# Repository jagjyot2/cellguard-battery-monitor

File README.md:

# CellGuard — Intelligent 21700 Li-Ion Battery Pack Monitor & Health Analytics

[-amber.svg)](./hardware/SAFETY-AND-TEST-PROCEDURE.md)

**CellGuard** (`cellguard-battery-monitor`) is an end-to-end embedded + hardware + analytics platform for monitoring **1S–6S 21700 Li-Ion battery packs** (optimized for **4S 14.8 V** and **6S 22.2 V** packs). It combines a KiCad 8 Kelvin-shunt instrumentation PCB, modular ESP32 PlatformIO C++ firmware, a BenchTwin digital-twin staging package, a FastAPI + SQLite analytics backend, and a dark-mode React + TypeScript telemetry dashboard.

> **CRITICAL SAFETY NOTICE**  
> **CellGuard is strictly a NON-INVASIVE, READ-ONLY telemetry and health analytics instrument.**  
> It **MUST ONLY** be used **alongside an external commercial BMS and an inline main fuse**.  
> CellGuard implements **NO cell balancing**, **NO battery charging**, and **NO high-current MOSFET switching**.  
> Review [`hardware/SAFETY-AND-TEST-PROCEDURE.md`](./hardware/SAFETY-AND-TEST-PROCEDURE.md) before applying power.

---

## Key Capabilities

- **Precision Current & Bus Sensing (`INA226`)**: 16-bit I2C shunt/bus monitoring across a **4-wire Kelvin `1.0 mΩ` shunt** with datasheet `CAL` register math, hardware `ALERT` interrupt (`GPIO16`), and 2-point gain/offset calibration.
- **Protected 1S–6S Cell Tap Monitoring**: `100 mA` PPTC polyfuses (`F1..F6`), `SMAJ28A` TVS surge clamping (`D1..D6`), `0.1%` high-impedance dividers, `BAT54S` ADC clamps, and an `8:1` analog MUX (`CD74HC4051` + `2.048 V` `LM4040` precision reference) with bus-sum cross-check.
- **4-Channel Thermal Runaway Array**: Steinhart-Hart NTC thermistor probes (`GPIO39/34/35/32`) with open/short wire fault detection and sliding-window OLS `dT/dt` (`°C/min`) thermal runaway derivative alarms.
- **Battery Health Analytics Engine**:
  - **OCV + Coulomb SoC Fusion**: Trapezoidal mAh/Wh integrator fused during rest with an IR-compensated 19-point 21700 NMC/INR OCV lookup table.
  - **Dynamic DC Internal Resistance (`R_dc = -ΔV / ΔI`)**: Automatic load-step resistance estimator tracking pack and per-cell impedance growth.
  - **State of Health (`SoH %`)**: Combines capacity retention fade and internal resistance growth.
- **Interactive Dashboard & CLI Calibration**: Dark-mode React + TypeScript UI served directly at `/`, 4S/6S bench discharge replay, configurable alarm rules, CSV history export, and `calibration_cli.py` + ESP32 NVS CRC16-protected serial calibration.

---

## Repository Structure

```text
06-CELLGUARD/
├── firmware/                  # PlatformIO ESP32 C++ firmware (INA226, NTC, MUX, Analytics, NVS CLI)
├── simulation/                # Simulator-independent HAL, Wokwi/BenchTwin adapters, scenarios & support matrix
├── wokwi/                     # Active Wokwi diagram.json, wokwi.toml, & custom I2C/MUX chip stubs
├── backend/                   # FastAPI REST API, SQLite DB, dataset replay & built dashboard assets
├── dashboard/                 # React + TypeScript + Vite dark-mode dashboard source
├── hardware/                  # KiCad 8 schematic, PCB, netlist, BOM, Gerbers & Safety Guide
├── benchtwin/                 # Preserved BenchTwin .btw workspace, JSON circuit, netlist, BOM & 3D STL enclosure
├── tests/                     # Pytest verification suite (INA226, SoC/SoH/R_dc, thermal, API/CLI, Wokwi/HAL)
├── docs/ARCHITECTURE.md       # Hardware/firmware math & system design specification
├── calibration_cli.py         # Two-point shunt & voltage divider calibration utility
└── ROADMAP.md                 # Engineering milestones & future roadmap
```

---

## Quick Start

### 1. Run Backend & Web Dashboard
```bash
pip install -r requirements.txt
uvicorn backend.main:app --host 127.0.0.1 --port 8006
```
Open **`http://127.0.0.1:8006/`** in your browser.

*(Optional)* Rebuild the React + TypeScript dashboard frontend into `backend/static/`:
```bash
cd dashboard
npm install
npm run build
```

### 2. Build ESP32 Firmware & Run Wokwi Simulation
```bash
cd firmware
pio run
```
`wokwi/wokwi.toml` points directly to `firmware/.pio/build/esp32dev/firmware.bin` and `firmware.elf`.
- Open `wokwi/` in VS Code with the **Wokwi Simulator** extension, or run headless with `WOKWI_CLI_TOKEN` set (`wokwi-cli wokwi --timeout 10000`).
- See [`wokwi/README.md`](./wokwi/README.md) and [`simulation/documentation/COMPONENT-SUPPORT-MATRIX.md`](./simulation/documentation/COMPONENT-SUPPORT-MATRIX.md) for natively supported Wokwi parts (`board-esp32-devkit-c-v4`, `wokwi-ntc-temperature-sensor`, `wokwi-potentiometer`, `wokwi-led`) vs. custom chips (`chip-ina226`, `chip-cd74hc4051`).
- **BenchTwin Reactivation**: The original `benchtwin/` digital-twin package is preserved intact; see [`simulation/adapters/benchtwin/README.md`](./simulation/adapters/benchtwin/README.md) to reactivate BenchTwin in the future.

### 3. Run Calibration CLI Utility
```bash
python calibration_cli.py --series-cells 4 --capacity-mah 5000 --shunt-mohm 1.0 \
  --curr-meas1 0.02 --curr-ref1 0.00 --curr-meas2 19.85 --curr-ref2 20.00
```

### 4. Run Automated Test Suite
```bash
pytest -v
```

---

## Documentation
- [Hardware Safety & Conservative Bench Test Procedure](./hardware/SAFETY-AND-TEST-PROCEDURE.md)
- [PCB Assembly & Calibration Guide](./hardware/ASSEMBLY-GUIDE.md)
- [System Architecture & Analytics Math](./docs/ARCHITECTURE.md)
- [Wokwi Simulation Setup](./wokwi/README.md)
- [Simulation Component Support Matrix](./simulation/documentation/COMPONENT-SUPPORT-MATRIX.md)
- [BenchTwin Adapter & Reactivation Guide](./simulation/adapters/benchtwin/README.md)
- [BenchTwin Simulation Notes](./benchtwin/BENCHTWIN-SIMULATION-NOTES.md)
- [Development Roadmap](./ROADMAP.md)

## License
Released under the [MIT License](./LICENSE).

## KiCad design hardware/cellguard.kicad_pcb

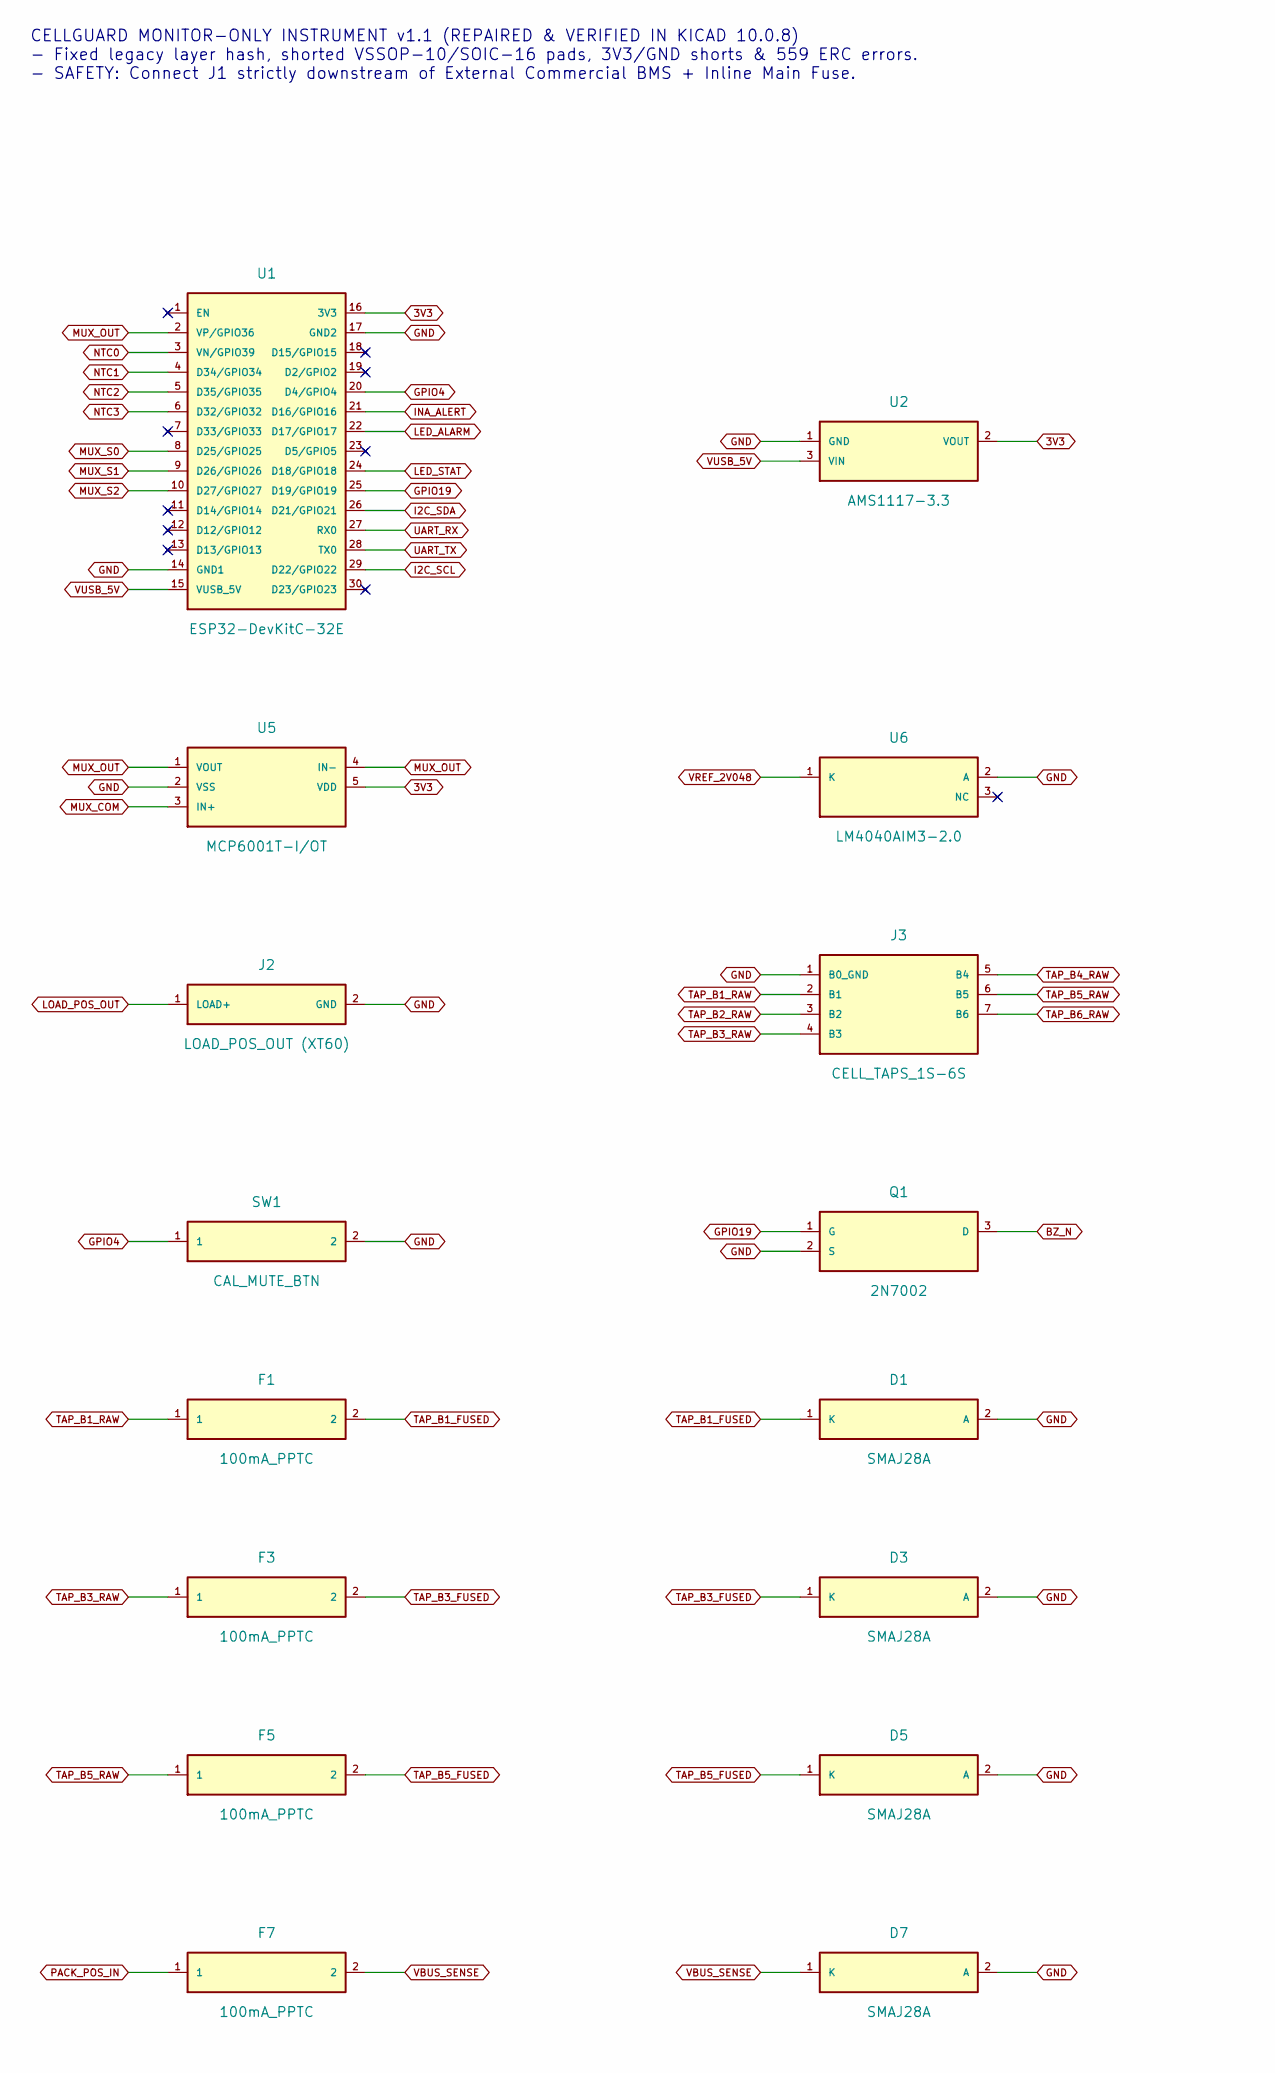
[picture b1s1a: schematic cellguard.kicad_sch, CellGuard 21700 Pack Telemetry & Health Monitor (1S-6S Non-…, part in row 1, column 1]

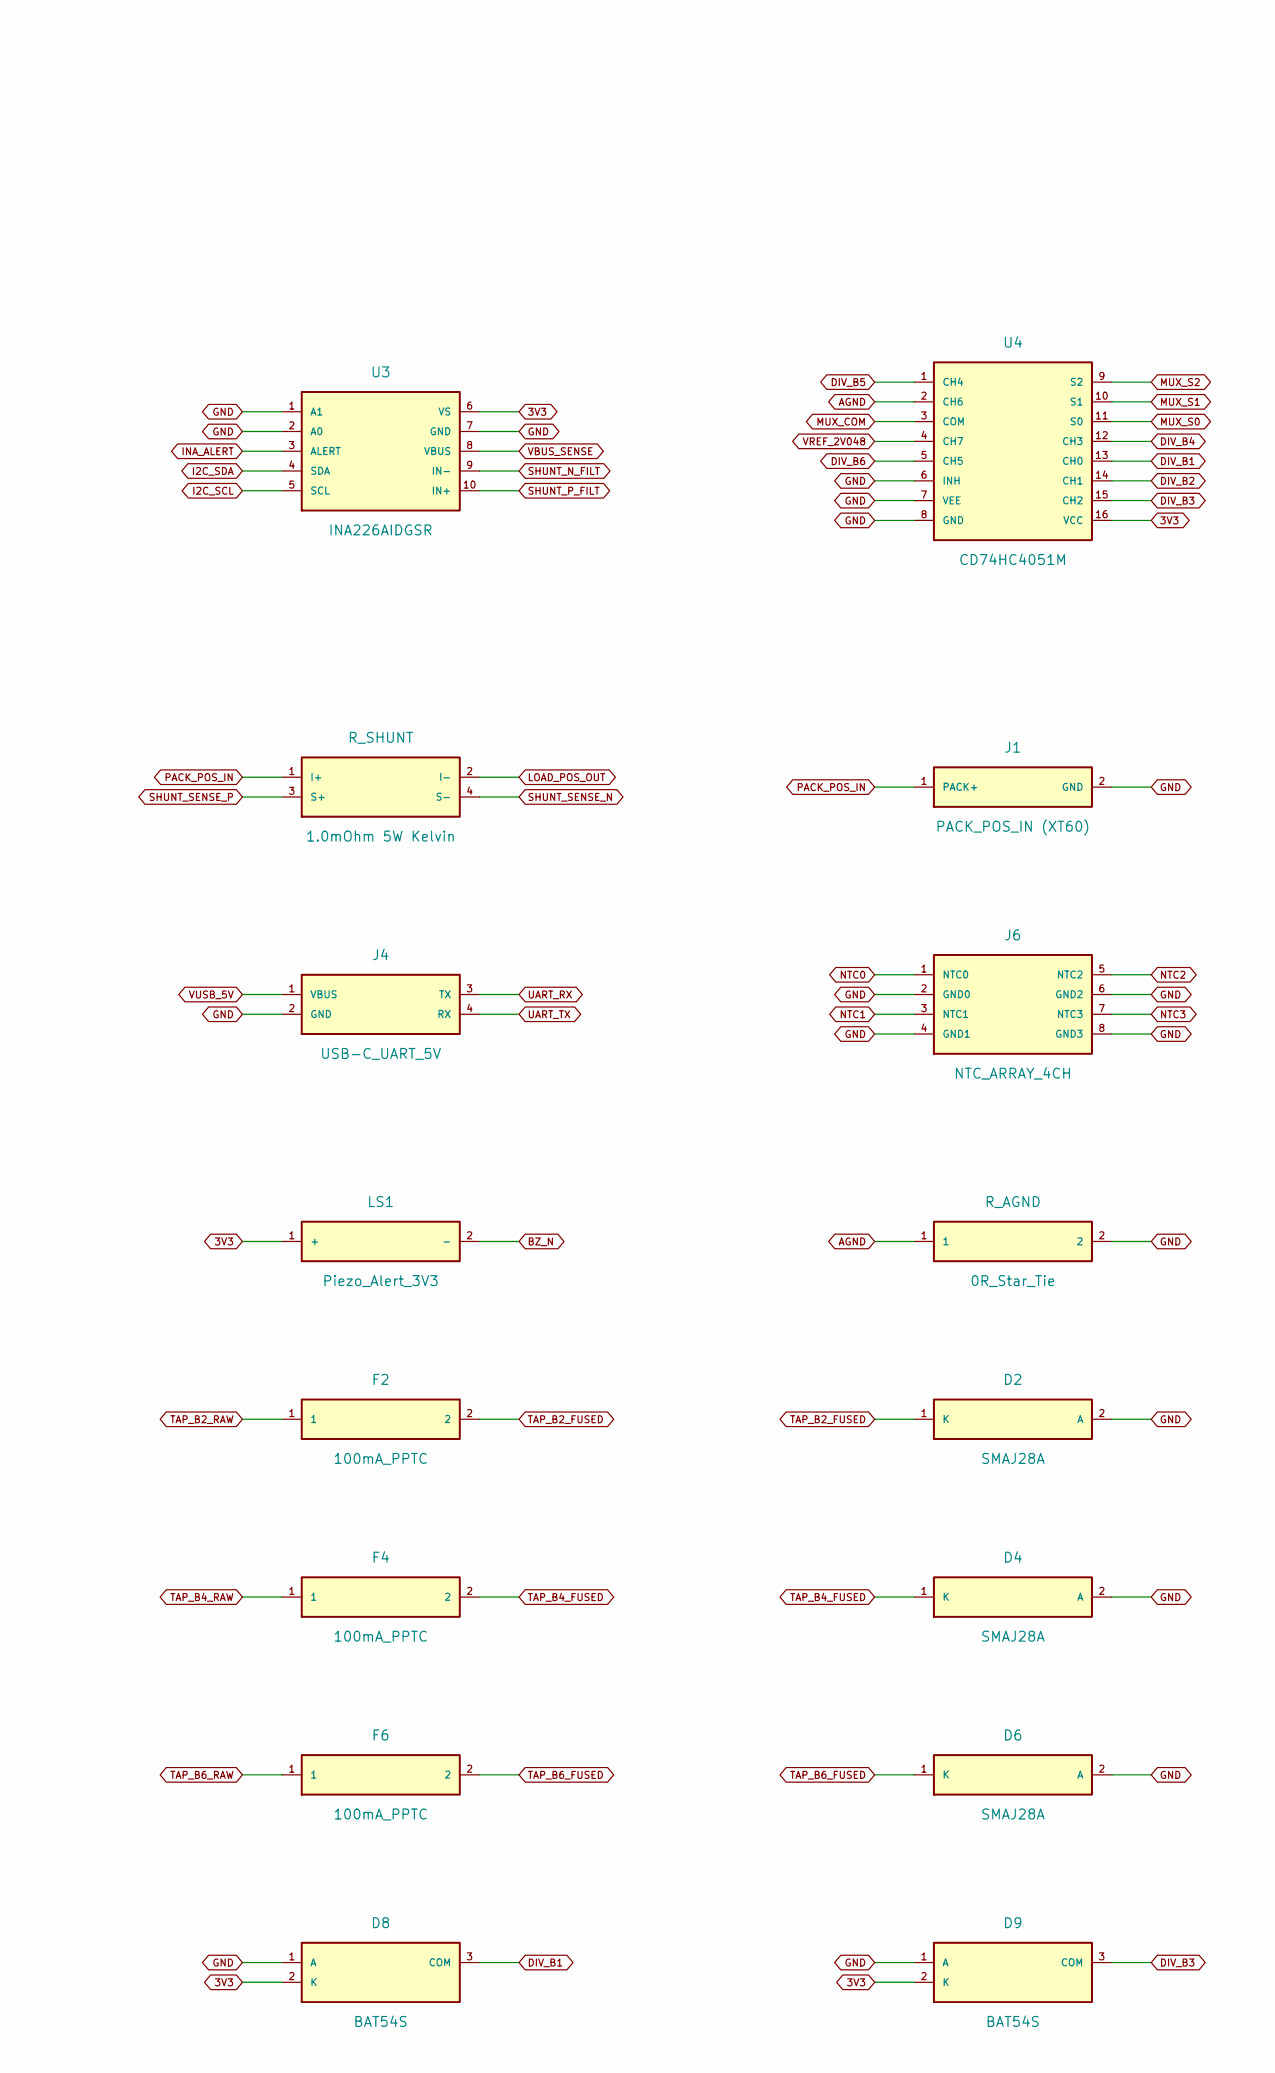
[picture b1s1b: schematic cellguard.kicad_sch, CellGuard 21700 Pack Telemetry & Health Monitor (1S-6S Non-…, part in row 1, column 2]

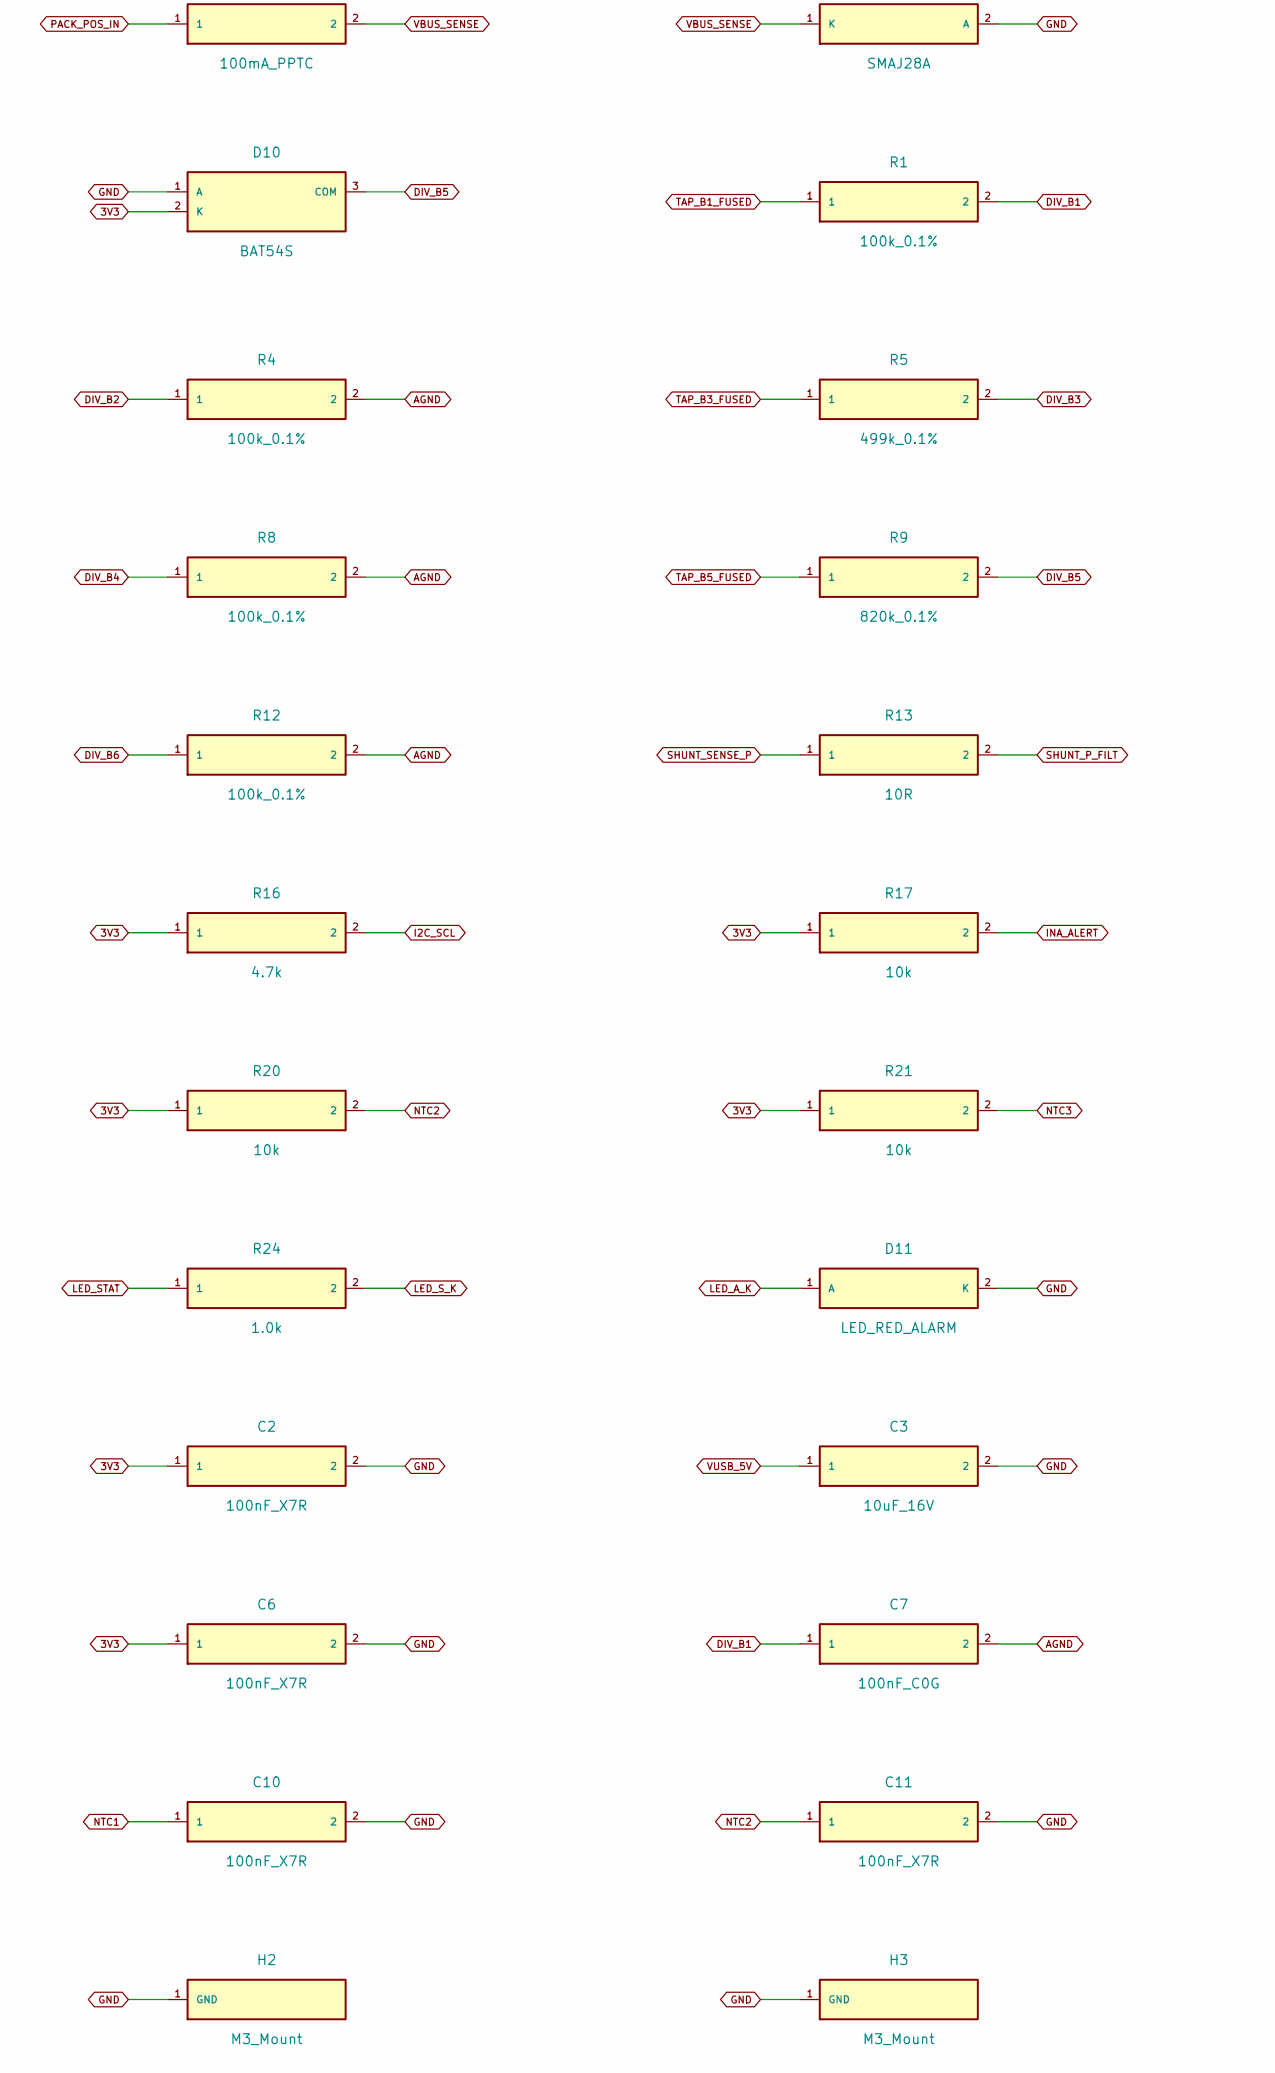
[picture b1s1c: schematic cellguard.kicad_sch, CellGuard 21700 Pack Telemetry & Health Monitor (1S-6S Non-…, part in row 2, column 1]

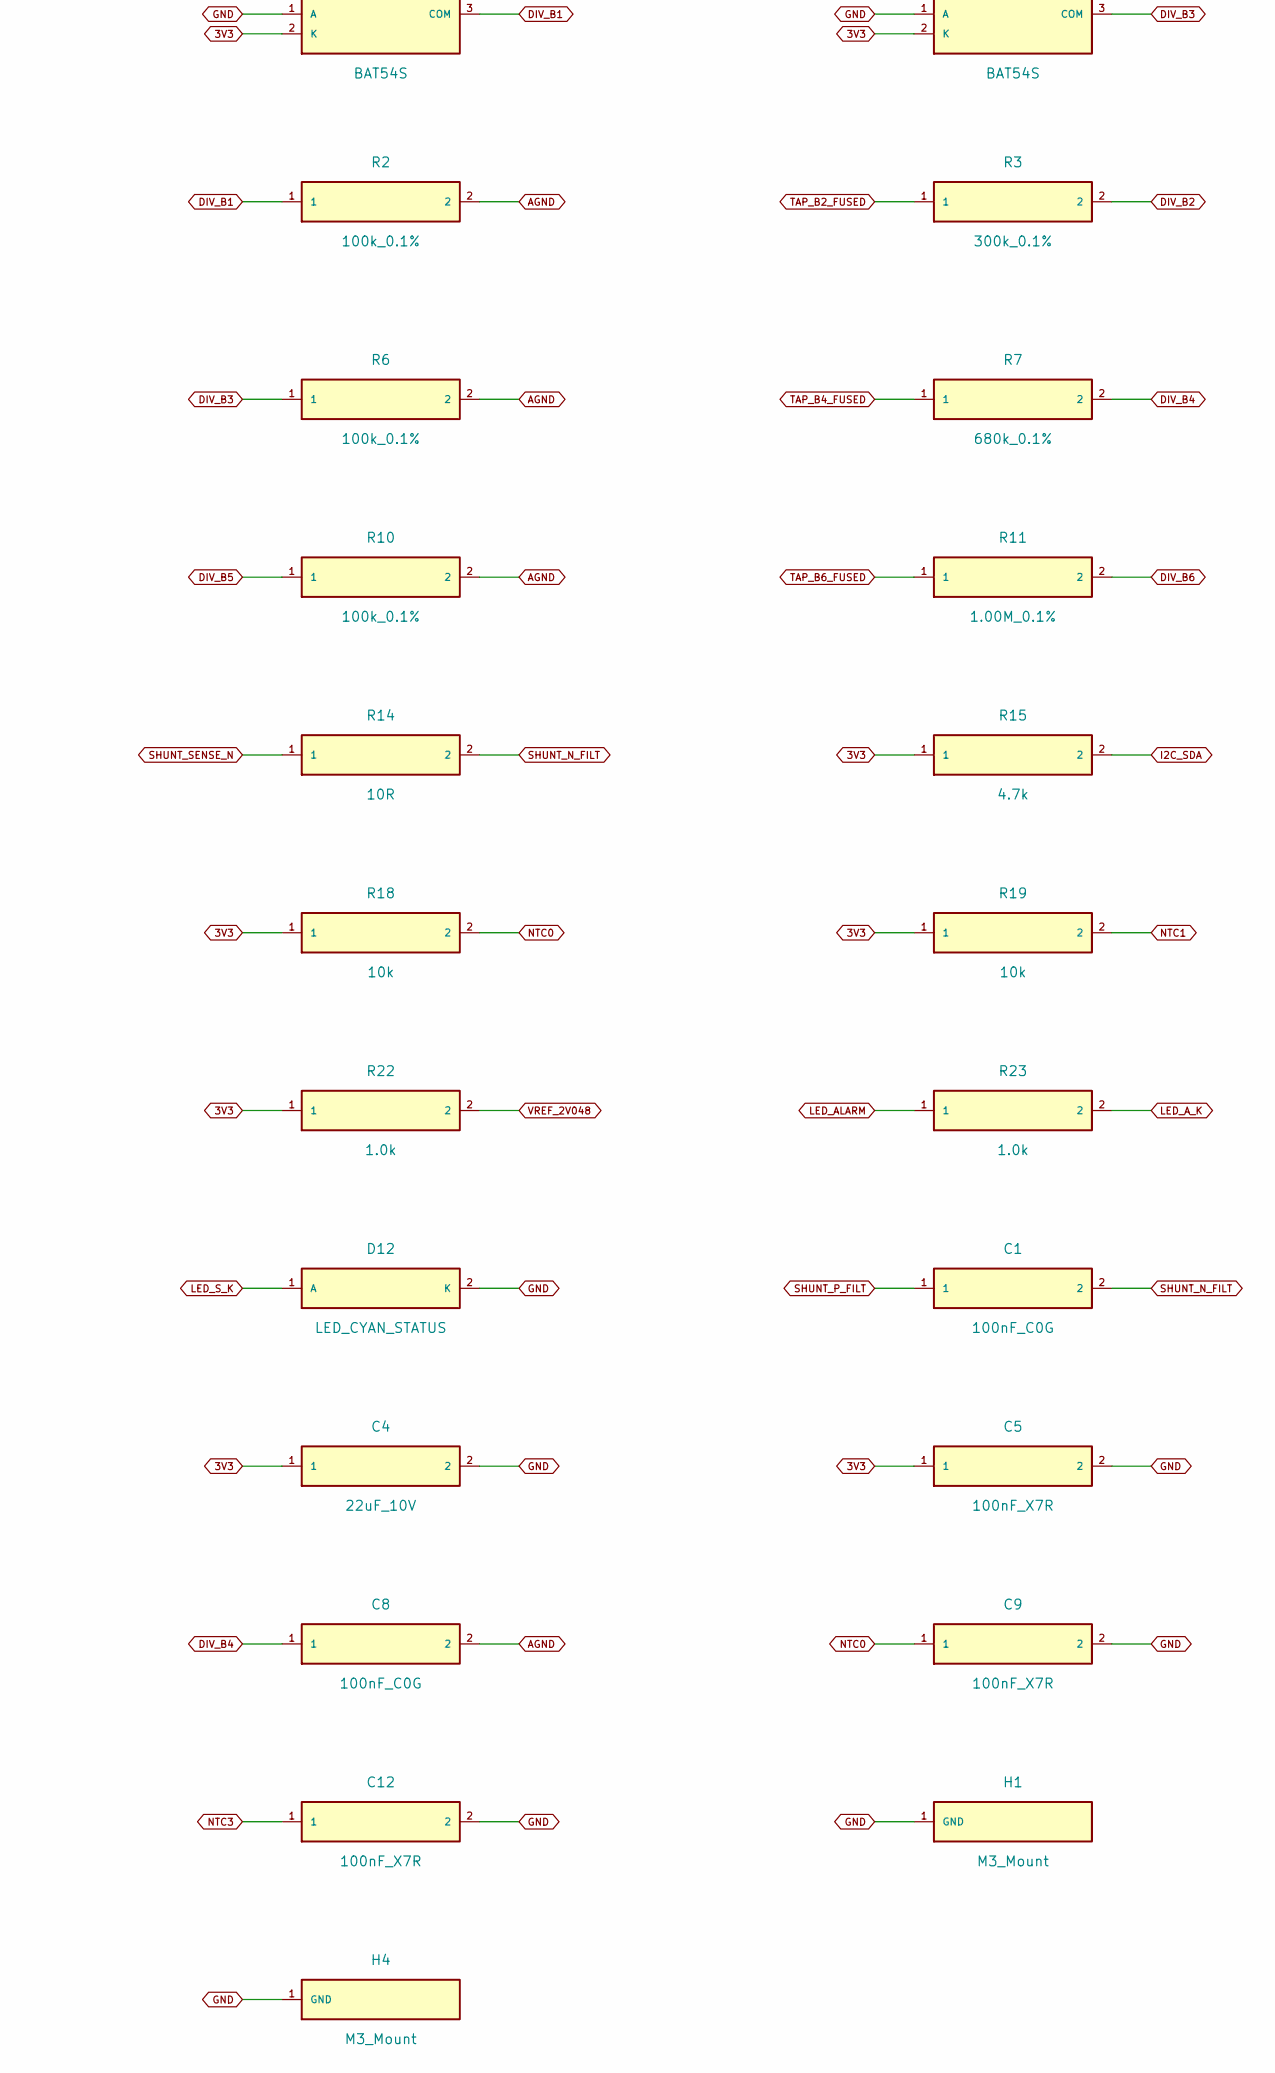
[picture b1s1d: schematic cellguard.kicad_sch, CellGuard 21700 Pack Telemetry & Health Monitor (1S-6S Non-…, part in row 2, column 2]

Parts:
C1, C7, C8: 100nF_C0G; SMD_0805; Rating 50V
C2, C5, C6, C9, C10, C11, C12: 100nF_X7R; SMD_0805; Rating 50V
C3: 10uF_16V; SMD_0805; Rating 50V
C4: 22uF_10V; SMD_0805; Rating 50V
D1, D2, D3, D4, D5, D6, D7: SMAJ28A; D_SMA; Rating 28V TVS; MPN SMAJ28A
D8, D9, D10: BAT54S; SOT-23; Rating 30V Clamp; MPN BAT54S
D11: LED_RED_ALARM; SMD_0805; Rating 2.0V
D12: LED_CYAN_STATUS; SMD_0805; Rating 3.0V
F1, F2, F3, F4, F5, F6, F7: 100mA_PPTC; SMD_0805; Rating 60V / 100mA; MPN 0805L010YR
H1, H2, H3, H4: M3_Mount; MountingHole_3.2mm_M3_Pad_Via; Rating M3
J1: PACK_POS_IN (XT60); AMASS_XT60_Vertical; Rating 60A / 28V; MPN XT60PW-M
J2: LOAD_POS_OUT (XT60); AMASS_XT60_Vertical; Rating 60A / 28V; MPN XT60PW-F
J3: CELL_TAPS_1S-6S; JST_XH_B7B-XH-A_1x07_P2.50mm_Vertical; Rating 28V / 1A Sense; MPN B7B-XH-A
J4: USB-C_UART_5V; PinHeader_1x04_P2.54mm; Rating 5V / 1A; MPN USB-C-UART-4P
J6: NTC_ARRAY_4CH; JST_XH_B8B-XH-A_1x08_P2.50mm_Horizontal; Rating 3.3V NTC; MPN B8B-XH-A
LS1: Piezo_Alert_3V3; PinHeader_1x02_P2.54mm; Rating 3.3V Piezo; MPN MLT-8530
Q1: 2N7002; SOT-23; Rating 60V / 300mA; MPN 2N7002K
R1, R2, R4, R6, R8, R10, R12: 100k_0.1%; SMD_0805; Rating 0.1%
R3: 300k_0.1%; SMD_0805; Rating 0.1%
R5: 499k_0.1%; SMD_0805; Rating 0.1%
R7: 680k_0.1%; SMD_0805; Rating 0.1%
R9: 820k_0.1%; SMD_0805; Rating 0.1%
R11: 1.00M_0.1%; SMD_0805; Rating 0.1%
R13, R14: 10R; SMD_0805; Rating 50V / 0.125W
R15, R16: 4.7k; SMD_0805; Rating 50V / 0.125W
R17, R18, R19, R20, R21: 10k; SMD_0805; Rating 50V / 0.125W
R22, R23, R24: 1.0k; SMD_0805; Rating 50V / 0.125W
R_AGND: 0R_Star_Tie; SMD_0805; Rating 0R Star Bridge
R_SHUNT: 1.0mOhm 5W Kelvin; R_Shunt_4Wire_CSS4J_4026; Rating 1mOhm / 5W Kelvin; MPN CSS4J-4026R-1L00F
SW1: CAL_MUTE_BTN; SW_SPST_SMD; Rating 12V / 50mA; MPN TL3342F160QG
U1: ESP32-DevKitC-32E; ESP32_DevKitC_30P; Rating 3.3V IO / 5V USB; MPN ESP32-WROOM-32E-N4
U2: AMS1117-3.3; SOT-223-3_TabPin2; Rating 3.3V / 800mA; MPN AMS1117-3.3
U3: INA226AIDGSR; VSSOP-10_3x3mm_P0.5mm_R180; Rating 36V / 16-bit I2C; MPN INA226AIDGSR
U4: CD74HC4051M; SOIC-16_3.9x9.9mm_P1.27mm; Rating 8:1 Analog MUX; MPN CD74HC4051M96
U5: MCP6001T-I/OT; SOT-23-5; Rating 3.3V RRIO Buffer; MPN MCP6001T-I/OT
U6: LM4040AIM3-2.0; SOT-23; Rating 2.048V 0.1% Ref; MPN LM4040AIM3-2.0/NOPB

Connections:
3V3: C2.1, C4.1, C5.1, C6.1, D8.2 (K), D9.2 (K), D10.2 (K), LS1.1 (+), R15.1, R16.1, R17.1, R18.1, R19.1, R20.1, R21.1, R22.1, U1.16 (3V3), U2.2 (VOUT), U3.6 (VS), U4.16 (VCC), U5.5 (VDD)
AGND: C7.2, C8.2, R2.2, R4.2, R6.2, R8.2, R10.2, R12.2, R_AGND.1, U4.2 (CH6)
BZ_N: LS1.2 (-), Q1.3 (D)
DIV_B1: C7.1, D8.3 (COM), R1.2, R2.1, U4.13 (CH0)
DIV_B2: R3.2, R4.1, U4.14 (CH1)
DIV_B3: D9.3 (COM), R5.2, R6.1, U4.15 (CH2)
DIV_B4: C8.1, R7.2, R8.1, U4.12 (CH3)
DIV_B5: D10.3 (COM), R9.2, R10.1, U4.1 (CH4)
DIV_B6: R11.2, R12.1, U4.5 (CH5)
GND: C2.2, C3.2, C4.2, C5.2, C6.2, C9.2, C10.2, C11.2, C12.2, D1.2 (A), D2.2 (A), D3.2 (A), D4.2 (A), D5.2 (A), D6.2 (A), D7.2 (A), D8.1 (A), D9.1 (A), D10.1 (A), D11.2 (K), D12.2 (K), H1.1, H2.1, H3.1, H4.1, J1.2 (GND), J2.2 (GND), J3.1 (B0_GND), J4.2 (GND), J6.2 (GND0), J6.4 (GND1), J6.6 (GND2), J6.8 (GND3), Q1.2 (S), R_AGND.2, SW1.2, U1.14 (GND1), U1.17 (GND2), U2.1 (GND), U3.1 (A1), U3.2 (A0), U3.7 (GND), U4.6 (INH), U4.7 (VEE), U4.8 (GND), U5.2 (VSS), U6.2 (A)
GPIO4: SW1.1, U1.20 (D4/GPIO4)
GPIO19: Q1.1 (G), U1.25 (D19/GPIO19)
I2C_SCL: R16.2, U1.29 (D22/GPIO22), U3.5 (SCL)
I2C_SDA: R15.2, U1.26 (D21/GPIO21), U3.4 (SDA)
INA_ALERT: R17.2, U1.21 (D16/GPIO16), U3.3 (ALERT)
LED_ALARM: R23.1, U1.22 (D17/GPIO17)
LED_A_K: D11.1 (A), R23.2
LED_STAT: R24.1, U1.24 (D18/GPIO18)
LED_S_K: D12.1 (A), R24.2
LOAD_POS_OUT: J2.1 (LOAD+), R_SHUNT.2 (I-)
MUX_COM: U4.3 (COM), U5.3 (IN+)
MUX_OUT: U1.2 (VP/GPIO36), U5.1 (VOUT), U5.4 (IN-)
MUX_S0: U1.8 (D25/GPIO25), U4.11 (S0)
MUX_S1: U1.9 (D26/GPIO26), U4.10 (S1)
MUX_S2: U1.10 (D27/GPIO27), U4.9 (S2)
NTC0: C9.1, J6.1 (NTC0), R18.2, U1.3 (VN/GPIO39)
NTC1: C10.1, J6.3 (NTC1), R19.2, U1.4 (D34/GPIO34)
NTC2: C11.1, J6.5 (NTC2), R20.2, U1.5 (D35/GPIO35)
NTC3: C12.1, J6.7 (NTC3), R21.2, U1.6 (D32/GPIO32)
PACK_POS_IN: F7.1, J1.1 (PACK+), R_SHUNT.1 (I+)
SHUNT_N_FILT: C1.2, R14.2, U3.9 (IN-)
SHUNT_P_FILT: C1.1, R13.2, U3.10 (IN+)
SHUNT_SENSE_N: R14.1, R_SHUNT.4 (S-)
SHUNT_SENSE_P: R13.1, R_SHUNT.3 (S+)
TAP_B1_FUSED: D1.1 (K), F1.2, R1.1
TAP_B1_RAW: F1.1, J3.2 (B1)
TAP_B2_FUSED: D2.1 (K), F2.2, R3.1
TAP_B2_RAW: F2.1, J3.3 (B2)
TAP_B3_FUSED: D3.1 (K), F3.2, R5.1
TAP_B3_RAW: F3.1, J3.4 (B3)
TAP_B4_FUSED: D4.1 (K), F4.2, R7.1
TAP_B4_RAW: F4.1, J3.5 (B4)
TAP_B5_FUSED: D5.1 (K), F5.2, R9.1
TAP_B5_RAW: F5.1, J3.6 (B5)
TAP_B6_FUSED: D6.1 (K), F6.2, R11.1
TAP_B6_RAW: F6.1, J3.7 (B6)
UART_RX: J4.3 (TX), U1.27 (RX0)
UART_TX: J4.4 (RX), U1.28 (TX0)
VBUS_SENSE: D7.1 (K), F7.2, U3.8 (VBUS)
VREF_2V048: R22.2, U4.4 (CH7), U6.1 (K)
VUSB_5V: C3.1, J4.1 (VBUS), U1.15 (VUSB_5V), U2.3 (VIN)

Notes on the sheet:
CELLGUARD MONITOR-ONLY INSTRUMENT v1.1 (REPAIRED & VERIFIED IN KICAD 10.0.8) - Fixed legacy layer hash, shorted VSSOP-10/SOIC-16 pads, 3V3/GND shorts & 559 ERC errors. - SAFETY: Connect J1 strictly downstream of External Commercial BMS + Inline Main Fuse.

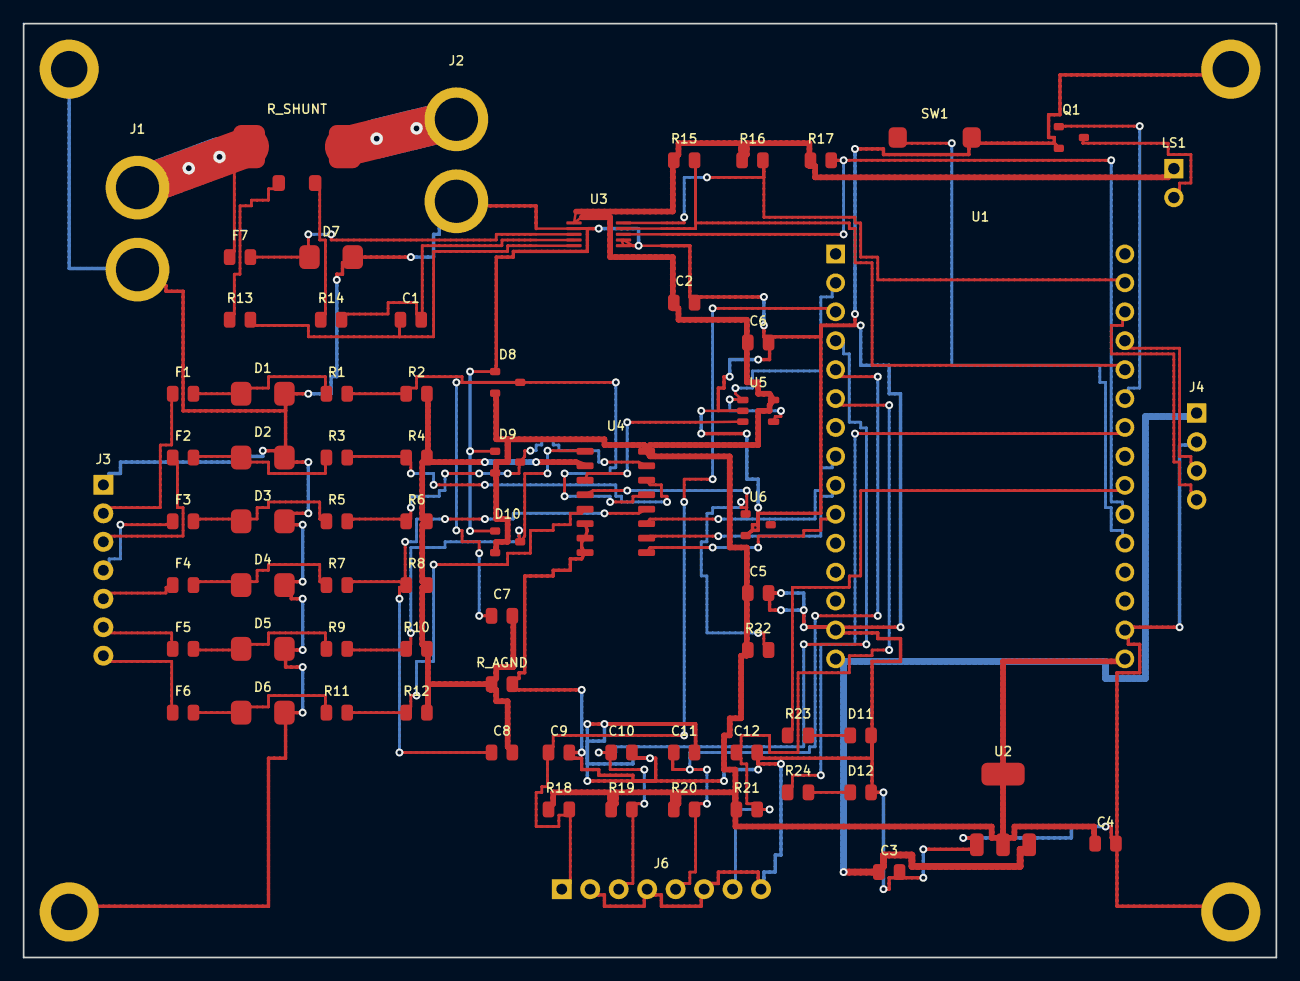
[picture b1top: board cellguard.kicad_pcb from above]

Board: 2 copper layers, 110.0 x 82.0 mm, 75 parts (0 on the bottom side), 51 nets.

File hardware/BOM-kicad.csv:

"Designator","Value","Footprint","MPN","Manufacturer","Rating","Qty"
"C1","100nF_C0G","CellGuard:SMD_0805","","","50V","1"
"C2","100nF_X7R","CellGuard:SMD_0805","","","50V","1"
"C3","10uF_16V","CellGuard:SMD_0805","","","50V","1"
"C4","22uF_10V","CellGuard:SMD_0805","","","50V","1"
"C5","100nF_X7R","CellGuard:SMD_0805","","","50V","1"
"C6","100nF_X7R","CellGuard:SMD_0805","","","50V","1"
"C7","100nF_C0G","CellGuard:SMD_0805","","","50V","1"
"C8","100nF_C0G","CellGuard:SMD_0805","","","50V","1"
"C9","100nF_X7R","CellGuard:SMD_0805","","","50V","1"
"C10","100nF_X7R","CellGuard:SMD_0805","","","50V","1"
"C11","100nF_X7R","CellGuard:SMD_0805","","","50V","1"
"C12","100nF_X7R","CellGuard:SMD_0805","","","50V","1"
"D1","SMAJ28A","CellGuard:D_SMA","SMAJ28A","","28V TVS","1"
"D2","SMAJ28A","CellGuard:D_SMA","SMAJ28A","","28V TVS","1"
"D3","SMAJ28A","CellGuard:D_SMA","SMAJ28A","","28V TVS","1"
"D4","SMAJ28A","CellGuard:D_SMA","SMAJ28A","","28V TVS","1"
"D5","SMAJ28A","CellGuard:D_SMA","SMAJ28A","","28V TVS","1"
"D6","SMAJ28A","CellGuard:D_SMA","SMAJ28A","","28V TVS","1"
"D7","SMAJ28A","CellGuard:D_SMA","SMAJ28A","","28V TVS","1"
"D8","BAT54S","CellGuard:SOT-23","BAT54S","","30V Clamp","1"
"D9","BAT54S","CellGuard:SOT-23","BAT54S","","30V Clamp","1"
"D10","BAT54S","CellGuard:SOT-23","BAT54S","","30V Clamp","1"
"D11","LED_RED_ALARM","CellGuard:SMD_0805","","","2.0V","1"
"D12","LED_CYAN_STATUS","CellGuard:SMD_0805","","","3.0V","1"
"F1","100mA_PPTC","CellGuard:SMD_0805","0805L010YR","","60V / 100mA","1"
"F2","100mA_PPTC","CellGuard:SMD_0805","0805L010YR","","60V / 100mA","1"
"F3","100mA_PPTC","CellGuard:SMD_0805","0805L010YR","","60V / 100mA","1"
"F4","100mA_PPTC","CellGuard:SMD_0805","0805L010YR","","60V / 100mA","1"
"F5","100mA_PPTC","CellGuard:SMD_0805","0805L010YR","","60V / 100mA","1"
"F6","100mA_PPTC","CellGuard:SMD_0805","0805L010YR","","60V / 100mA","1"
"F7","100mA_PPTC","CellGuard:SMD_0805","0805L010YR","","60V / 100mA","1"
"H1","M3_Mount","CellGuard:MountingHole_3.2mm_M3_Pad_Via","","","M3","1"
"H2","M3_Mount","CellGuard:MountingHole_3.2mm_M3_Pad_Via","","","M3","1"
"H3","M3_Mount","CellGuard:MountingHole_3.2mm_M3_Pad_Via","","","M3","1"
"H4","M3_Mount","CellGuard:MountingHole_3.2mm_M3_Pad_Via","","","M3","1"
"J1","PACK_POS_IN (XT60)","CellGuard:AMASS_XT60_Vertical","XT60PW-M","","60A / 28V","1"
"J2","LOAD_POS_OUT (XT60)","CellGuard:AMASS_XT60_Vertical","XT60PW-F","","60A / 28V","1"
"J3","CELL_TAPS_1S-6S","CellGuard:JST_XH_B7B-XH-A_1x07_P2.50mm_Vertical","B7B-XH-A","JST","28V / 1A Sense","1"
"J4","USB-C_UART_5V","CellGuard:PinHeader_1x04_P2.54mm","USB-C-UART-4P","","5V / 1A","1"
"J6","NTC_ARRAY_4CH","CellGuard:JST_XH_B8B-XH-A_1x08_P2.50mm_Horizontal","B8B-XH-A","JST","3.3V NTC","1"
"LS1","Piezo_Alert_3V3","CellGuard:PinHeader_1x02_P2.54mm","MLT-8530","","3.3V Piezo","1"
"Q1","2N7002","CellGuard:SOT-23","2N7002K","","60V / 300mA","1"
"R1","100k_0.1%","CellGuard:SMD_0805","","","0.1%","1"
"R2","100k_0.1%","CellGuard:SMD_0805","","","0.1%","1"
"R3","300k_0.1%","CellGuard:SMD_0805","","","0.1%","1"
"R4","100k_0.1%","CellGuard:SMD_0805","","","0.1%","1"
"R5","499k_0.1%","CellGuard:SMD_0805","","","0.1%","1"
"R6","100k_0.1%","CellGuard:SMD_0805","","","0.1%","1"
"R7","680k_0.1%","CellGuard:SMD_0805","","","0.1%","1"
"R8","100k_0.1%","CellGuard:SMD_0805","","","0.1%","1"
"R9","820k_0.1%","CellGuard:SMD_0805","","","0.1%","1"
"R10","100k_0.1%","CellGuard:SMD_0805","","","0.1%","1"
"R11","1.00M_0.1%","CellGuard:SMD_0805","","","0.1%","1"
"R12","100k_0.1%","CellGuard:SMD_0805","","","0.1%","1"
"R13","10R","CellGuard:SMD_0805","","","50V / 0.125W","1"
"R14","10R","CellGuard:SMD_0805","","","50V / 0.125W","1"
"R15","4.7k","CellGuard:SMD_0805","","","50V / 0.125W","1"
"R16","4.7k","CellGuard:SMD_0805","","","50V / 0.125W","1"
"R17","10k","CellGuard:SMD_0805","","","50V / 0.125W","1"
"R18","10k","CellGuard:SMD_0805","","","50V / 0.125W","1"
"R19","10k","CellGuard:SMD_0805","","","50V / 0.125W","1"
"R20","10k","CellGuard:SMD_0805","","","50V / 0.125W","1"
"R21","10k","CellGuard:SMD_0805","","","50V / 0.125W","1"
"R22","1.0k","CellGuard:SMD_0805","","","50V / 0.125W","1"
"R23","1.0k","CellGuard:SMD_0805","","","50V / 0.125W","1"
"R24","1.0k","CellGuard:SMD_0805","","","50V / 0.125W","1"
"R_AGND?","0R_Star_Tie","CellGuard:SMD_0805","","","0R Star Bridge","1"
"R_SHUNT?","1.0mOhm 5W Kelvin","CellGuard:R_Shunt_4Wire_CSS4J_4026","CSS4J-4026R-1L00F","Bourns","1mOhm / 5W Kelvin","1"
"SW1","CAL_MUTE_BTN","CellGuard:SW_SPST_SMD","TL3342F160QG","","12V / 50mA","1"
"U1","ESP32-DevKitC-32E","CellGuard:ESP32_DevKitC_30P","ESP32-WROOM-32E-N4","Espressif","3.3V IO / 5V USB","1"
"U2","AMS1117-3.3","CellGuard:SOT-223-3_TabPin2","AMS1117-3.3","AMS","3.3V / 800mA","1"
"U3","INA226AIDGSR","CellGuard:VSSOP-10_3x3mm_P0.5mm_R180","INA226AIDGSR","Texas Instruments","36V / 16-bit I2C","1"
"U4","CD74HC4051M","CellGuard:SOIC-16_3.9x9.9mm_P1.27mm","CD74HC4051M96","Texas Instruments","8:1 Analog MUX","1"
"U5","MCP6001T-I/OT","CellGuard:SOT-23-5","MCP6001T-I/OT","Microchip","3.3V RRIO Buffer","1"
"U6","LM4040AIM3-2.0","CellGuard:SOT-23","LM4040AIM3-2.0/NOPB","Texas Instruments","2.048V 0.1% Ref","1"

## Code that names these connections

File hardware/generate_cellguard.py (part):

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            f"{LIB}:ESP32_DevKitC_30P",
            [
                kt.SchPin("1", "EN", "NC_EN", "left", "no_connect"),
                kt.SchPin("2", "VP/GPIO36", "MUX_OUT", "left"),
                kt.SchPin("3", "VN/GPIO39", "NTC0", "left"),
                kt.SchPin("4", "D34/GPIO34", "NTC1", "left"),
                kt.SchPin("5", "D35/GPIO35", "NTC2", "left"),
                kt.SchPin("6", "D32/GPIO32", "NTC3", "left"),
                kt.SchPin("7", "D33/GPIO33", "NC_D33", "left", "no_connect"),
                kt.SchPin("8", "D25/GPIO25", "MUX_S0", "left"),
                kt.SchPin("9", "D26/GPIO26", "MUX_S1", "left"),
                kt.SchPin("10", "D27/GPIO27", "MUX_S2", "left"),
                kt.SchPin("11", "D14/GPIO14", "NC_D14", "left", "no_connect"),
                kt.SchPin("12", "D12/GPIO12", "NC_D12", "left", "no_connect"),
                kt.SchPin("13", "D13/GPIO13", "NC_D13", "left", "no_connect"),
                kt.SchPin("14", "GND1", "GND", "left"),
                kt.SchPin("15", "VUSB_5V", "VUSB_5V", "left"),
                kt.SchPin("16", "3V3", "3V3", "right"),
                kt.SchPin("17", "GND2", "GND", "right"),
                kt.SchPin("18", "D15/GPIO15", "NC_D15", "right", "no_connect"),
                kt.SchPin("19", "D2/GPIO2", "NC_D2", "right", "no_connect"),
                kt.SchPin("20", "D4/GPIO4", "GPIO4", "right"),
                kt.SchPin("21", "D16/GPIO16", "INA_ALERT", "right"),
                kt.SchPin("22", "D17/GPIO17", "LED_ALARM", "right"),
                kt.SchPin("23", "D5/GPIO5", "NC_D5", "right", "no_connect"),
                kt.SchPin("24", "D18/GPIO18", "LED_STAT", "right"),
                kt.SchPin("25", "D19/GPIO19", "GPIO19", "right"),
                kt.SchPin("26", "D21/GPIO21", "I2C_SDA", "right"),
                kt.SchPin("27", "RX0", "UART_RX", "right"),
                kt.SchPin("28", "TX0", "UART_TX", "right"),
                kt.SchPin("29", "D22/GPIO22", "I2C_SCL", "right"),
                kt.SchPin("30", "D23/GPIO23", "NC_D23", "right", "no_connect"),
            ],
            mpn="ESP32-WROOM-32E-N4",
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    sb.add_component(kt.SchComponent("U2", "AMS1117-3.3", f"{LIB}:SOT-223-3_TabPin2", [
        kt.SchPin("1", "GND", "GND", "left"),
        kt.SchPin("2", "VOUT", "3V3", "right"),
        kt.SchPin("3", "VIN", "VUSB_5V", "left"),
    ], mpn="AMS1117-3.3", manufacturer="AMS", rating="3.3V / 800mA"))

    sb.add_component(kt.SchComponent("U3", "INA226AIDGSR", f"{LIB}:VSSOP-10_3x3mm_P0.5mm_R180", [
        kt.SchPin("1", "A1", "GND", "left"),
        kt.SchPin("2", "A0", "GND", "left"),
        kt.SchPin("3", "ALERT", "INA_ALERT", "left"),
        kt.SchPin("4", "SDA", "I2C_SDA", "left"),
        kt.SchPin("5", "SCL", "I2C_SCL", "left"),
        kt.SchPin("6", "VS", "3V3", "right"),
        kt.SchPin("7", "GND", "GND", "right"),
        kt.SchPin("8", "VBUS", "VBUS_SENSE", "right"),
        kt.SchPin("9", "IN-", "SHUNT_N_FILT", "right"),
        kt.SchPin("10", "IN+", "SHUNT_P_FILT", "right"),
    ], mpn="INA226AIDGSR", manufacturer="Texas Instruments", rating="36V / 16-bit I2C"))

    sb.add_component(kt.SchComponent("U4", "CD74HC4051M", f"{LIB}:SOIC-16_3.9x9.9mm_P1.27mm", [
        kt.SchPin("1", "CH4", "DIV_B5", "left"),
        kt.SchPin("2", "CH6", "AGND", "left"),
        kt.SchPin("3", "COM", "MUX_COM", "left"),
        kt.SchPin("4", "CH7", "VREF_2V048", "left"),
        kt.SchPin("5", "CH5", "DIV_B6", "left"),
        kt.SchPin("6", "INH", "GND", "left"),
        kt.SchPin("7", "VEE", "GND", "left"),
        kt.SchPin("8", "GND", "GND", "left"),
        kt.SchPin("9", "S2", "MUX_S2", "right"),
        kt.SchPin("10", "S1", "MUX_S1", "right"),
        kt.SchPin("11", "S0", "MUX_S0", "right"),
        kt.SchPin("12", "CH3", "DIV_B4", "right"),
        kt.SchPin("13", "CH0", "DIV_B1", "right"),
        kt.SchPin("14", "CH1", "DIV_B2", "right"),
        kt.SchPin("15", "CH2", "DIV_B3", "right"),
        kt.SchPin("16", "VCC", "3V3", "right"),
    ], mpn="CD74HC4051M96", manufacturer="Texas Instruments", rating="8:1 Analog MUX"))

    sb.add_component(kt.SchComponent("U5", "MCP6001T-I/OT", f"{LIB}:SOT-23-5", [
        kt.SchPin("1", "VOUT", "MUX_OUT", "left"),
        kt.SchPin("2", "VSS", "GND", "left"),
        kt.SchPin("3", "IN+", "MUX_COM", "left"),
        kt.SchPin("4", "IN-", "MUX_OUT", "right"),
        kt.SchPin("5", "VDD", "3V3", "right"),
    ], mpn="MCP6001T-I/OT", manufacturer="Microchip", rating="3.3V RRIO Buffer"))

    sb.add_component(kt.SchComponent("U6", "LM4040AIM3-2.0", f"{LIB}:SOT-23", [
        kt.SchPin("1", "K", "VREF_2V048", "left"),
        kt.SchPin("2", "A", "GND", "right"),
        kt.SchPin("3", "NC", "NC_U6", "right", "no_connect"),
    ], mpn="LM4040AIM3-2.0/NOPB", manufacturer="Texas Instruments", rating="2.048V 0.1% Ref"))

    sb.add_component(kt.SchComponent("R_SHUNT", "1.0mOhm 5W Kelvin", f"{LIB}:R_Shunt_4Wire_CSS4J_4026", [
        kt.SchPin("1", "I+", "PACK_POS_IN", "left"),
        kt.SchPin("2", "I-", "LOAD_POS_OUT", "right"),
        kt.SchPin("3", "S+", "SHUNT_SENSE_P", "left"),
        kt.SchPin("4", "S-", "SHUNT_SENSE_N", "right"),
    ], mpn="CSS4J-4026R-1L00F", manufacturer="Bourns", rating="1mOhm / 5W Kelvin"))

    sb.add_component(kt.SchComponent("J1", "PACK_POS_IN (XT60)", f"{LIB}:AMASS_XT60_Vertical", [kt.SchPin("1", "PACK+", "PACK_POS_IN", "left"), kt.SchPin("2", "GND", "GND", "right")], mpn="XT60PW-M", rating="60A / 28V"))
    sb.add_component(kt.SchComponent("J2", "LOAD_POS_OUT (XT60)", f"{LIB}:AMASS_XT60_Vertical", [kt.SchPin("1", "LOAD+", "LOAD_POS_OUT", "left"), kt.SchPin("2", "GND", "GND", "right")], mpn="XT60PW-F", rating="60A / 28V"))
    sb.add_component(kt.SchComponent("J3", "CELL_TAPS_1S-6S", f"{LIB}:JST_XH_B7B-XH-A_1x07_P2.50mm_Vertical", [
        kt.SchPin("1", "B0_GND", "GND", "left"),
        kt.SchPin("2", "B1", "TAP_B1_RAW", "left"),
        kt.SchPin("3", "B2", "TAP_B2_RAW", "left"),
        kt.SchPin("4", "B3", "TAP_B3_RAW", "left"),
        kt.SchPin("5", "B4", "TAP_B4_RAW", "right"),
        kt.SchPin("6", "B5", "TAP_B5_RAW", "right"),
        kt.SchPin("7", "B6", "TAP_B6_RAW", "right"),
    ], mpn="B7B-XH-A", manufacturer="JST", rating="28V / 1A Sense"))
    sb.add_component(kt.SchComponent("J4", "USB-C_UART_5V", f"{LIB}:PinHeader_1x04_P2.54mm", [
        kt.SchPin("1", "VBUS", "VUSB_5V", "left"),
        kt.SchPin("2", "GND", "GND", "left"),
        kt.SchPin("3", "TX", "UART_RX", "right"),
        kt.SchPin("4", "RX", "UART_TX", "right"),
    ], mpn="USB-C-UART-4P", rating="5V / 1A"))
    sb.add_component(kt.SchComponent("J6", "NTC_ARRAY_4CH", f"{LIB}:JST_XH_B8B-XH-A_1x08_P2.50mm_Horizontal", [
        kt.SchPin("1", "NTC0", "NTC0", "left"), kt.SchPin("2", "GND0", "GND", "left"),
        kt.SchPin("3", "NTC1", "NTC1", "left"), kt.SchPin("4", "GND1", "GND", "left"),
        kt.SchPin("5", "NTC2", "NTC2", "right"), kt.SchPin("6", "GND2", "GND", "right"),
        kt.SchPin("7", "NTC3", "NTC3", "right"), kt.SchPin("8", "GND3", "GND", "right"),
    ], mpn="B8B-XH-A", manufacturer="JST", rating="3.3V NTC"))

    sb.add_component(kt.SchComponent("SW1", "CAL_MUTE_BTN", f"{LIB}:SW_SPST_SMD", [kt.SchPin("1", "1", "GPIO4", "left"), kt.SchPin("2", "2", "GND", "right")], mpn="TL3342F160QG", rating="12V / 50mA"))
    sb.add_component(kt.SchComponent("Q1", "2N7002", f"{LIB}:SOT-23", [kt.SchPin("1", "G", "GPIO19", "left"), kt.SchPin("2", "S", "GND", "left"), kt.SchPin("3", "D", "BZ_N", "right")], mpn="2N7002K", rating="60V / 300mA"))
    sb.add_component(kt.SchComponent("LS1", "Piezo_Alert_3V3", f"{LIB}:PinHeader_1x02_P2.54mm", [kt.SchPin("1", "+", "3V3", "left"), kt.SchPin("2", "-", "BZ_N", "right")], mpn="MLT-8530", rating="3.3V Piezo"))
    sb.add_component(kt.SchComponent("R_AGND", "0R_Star_Tie", f"{LIB}:SMD_0805", [kt.SchPin("1", "1", "AGND", "left"), kt.SchPin("2", "2", "GND", "right")], rating="0R Star Bridge"))

    # F1..F7 (100mA PPTC) + D1..D7 (SMAJ28A TVS)
    for idx in range(1, 7):
        sb.add_component(kt.SchComponent(f"F{idx}", "100mA_PPTC", f"{LIB}:SMD_0805", [kt.SchPin("1", "1", f"TAP_B{idx}_RAW", "left"), kt.SchPin("2", "2", f"TAP_B{idx}_FUSED", "right")], mpn="0805L010YR", rating="60V / 100mA"))
        sb.add_component(kt.SchComponent(f"D{idx}", "SMAJ28A", f"{LIB}:D_SMA", [kt.SchPin("1", "K", f"TAP_B{idx}_FUSED", "left"), kt.SchPin("2", "A", "GND", "right")], mpn="SMAJ28A", rating="28V TVS"))
    sb.add_component(kt.SchComponent("F7", "100mA_PPTC", f"{LIB}:SMD_0805", [kt.SchPin("1", "1", "PACK_POS_IN", "left"), kt.SchPin("2", "2", "VBUS_SENSE", "right")], mpn="0805L010YR", rating="60V / 100mA"))
    sb.add_component(kt.SchComponent("D7", "SMAJ28A", f"{LIB}:D_SMA", [kt.SchPin("1", "K", "VBUS_SENSE", "left"), kt.SchPin("2", "A", "GND", "right")], mpn="SMAJ28A", rating="28V TVS"))

    for dref, dnet in [("D8", "DIV_B1"), ("D9", "DIV_B3"), ("D10", "DIV_B5")]:
        sb.add_component(kt.SchComponent(dref, "BAT54S", f"{LIB}:SOT-23", [kt.SchPin("1", "A", "GND", "left"), kt.SchPin("2", "K", "3V3", "left"), kt.SchPin("3", "COM", dnet, "right")], mpn="BAT54S", rating="30V Clamp"))
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

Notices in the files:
README.md:
License: MIT
